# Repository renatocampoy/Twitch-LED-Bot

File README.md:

## Twitch LED Bot - ESP8266

Criado por Eng. Renato Campoy.

Este projeto permite que você controle um strip de LED NeoPixel via comandos no chat da Twitch, utilizando a placa ESP8266. O código é escrito em C++ e utiliza a biblioteca WiFiManager para gerenciar a conexão Wi-Fi e a biblioteca Adafruit NeoPixel para controlar o strip de LED.

## Token da Twitch

Para usar este código, você precisará de um token de OAuth da Twitch. Aqui estão as etapas para obtê-lo:

1.  Acesse [https://twitchapps.com/tmi/](https://twitchapps.com/tmi/)
2.  Clique em 'Connect' e autorize o acesso ao seu canal.
3.  Copie o token gerado. Este é o seu token OAuth, que permite que o bot envie mensagens ao seu canal.

Tenha em mente que este token é equivalente à senha da sua conta da Twitch. Não compartilhe com ninguém.

### Dependências

Você precisará das seguintes bibliotecas para usar este projeto:

-   ESP8266WiFi
-   DNSServer
-   ESP8266WebServer
-   WiFiManager
-   EEPROM
-   Adafruit_NeoPixel

Estas bibliotecas podem ser instaladas através do Gerenciador de Bibliotecas do Arduino.

## Instalação

1.  Clone este repositório.
2.  Abra o arquivo `.ino` no Arduino IDE.
3.  Carregue o código para o ESP8266.

## Configuração

1.  Ao ligar o ESP, uma rede wifi com o nome LEDBOT_AP aparecerá, conecte-se a ela.
2.  Ao conectar, aparecerá uma pagina onde você deve clicar em "Configure WIFI"
3.  Clique na sua REDE, entre com a senha.
4. Em "Nick" é o seu usuário da Twitch tudo em minúsculo 
5. Em Token você vai colocar o token gerado no tópico "Token da Twitch"

## Uso

Uma vez que o código esteja funcionando, você poderá enviar comandos para o chat da Twitch para controlar a iluminação do strip de LED. Aqui estão alguns exemplos de comandos que você pode usar:

-   `!led vermelho`: muda a cor do LED para vermelho.
-   `!led #ff00ff`: muda a cor do LED para o valor hexadecimal fornecido (neste caso, magenta).
-   `!led cores`: lista todas as cores disponíveis.

Além disso, o bot responde a comandos enviados via interface serial para reiniciar o ESP ou redefinir as configurações de WiFi ou Twitch. (vide código)

## Contribuição

Este é um projeto open-source. Se tiver alguma sugestão ou melhoria, por favor, faça um fork do repositório e envie uma pull request.

## Problemas Conhecidos

Atualmente, o bot não responde a erros do servidor da Twitch. Se você experimentar algum problema, tente reiniciar o ESP.

## Licença

Este projeto está licenciado sob a Licença GPLv3 - veja o arquivo [LICENSE](https://www.gnu.org/licenses/gpl-3.0.pt-br.html) para mais detalhes.

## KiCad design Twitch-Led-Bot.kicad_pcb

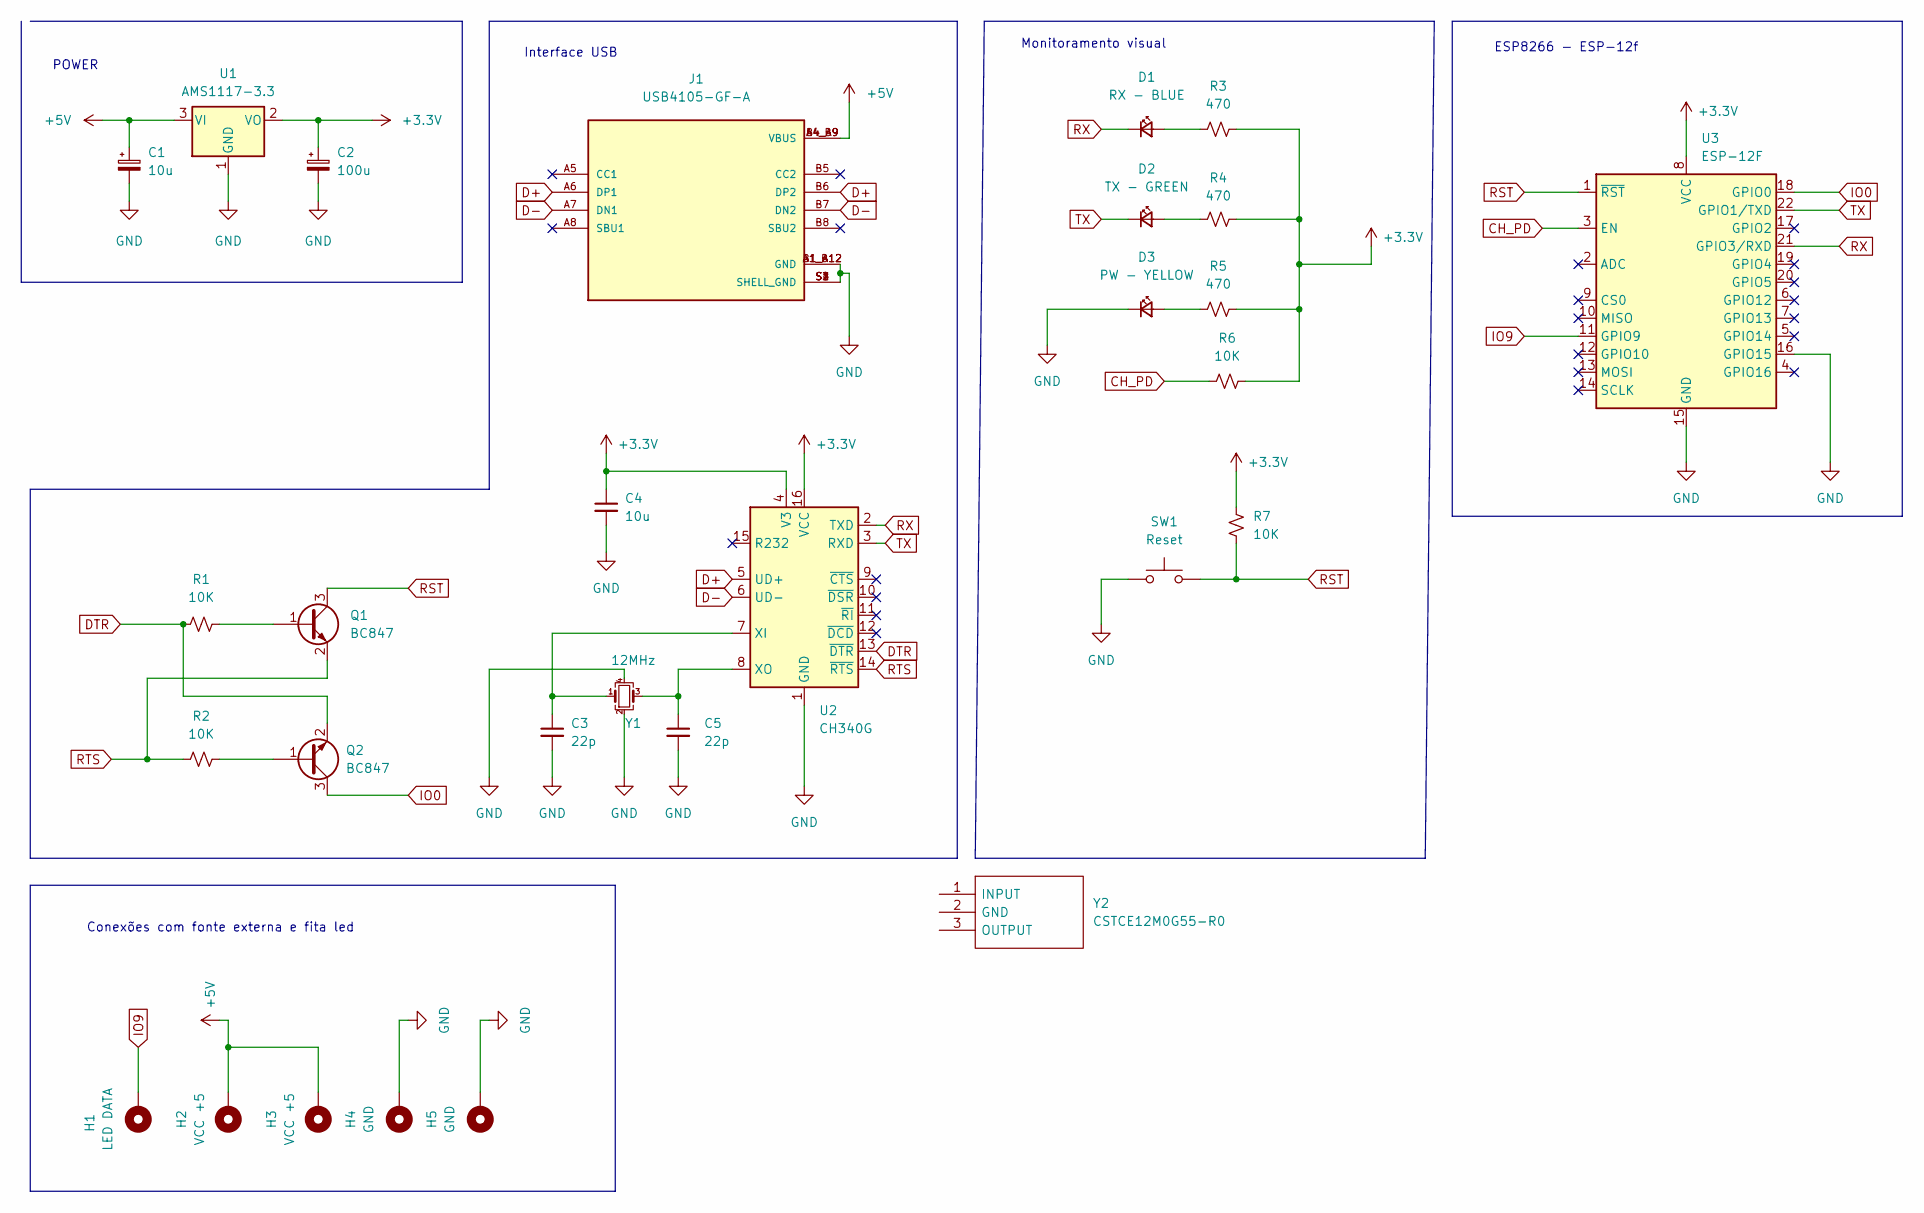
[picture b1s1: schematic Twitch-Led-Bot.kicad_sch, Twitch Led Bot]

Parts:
C1, C4: 10u; C_0805_2012Metric
C2: 100u; C_0805_2012Metric
C3, C5: 22p; C_0805_2012Metric
D1: RX - BLUE; LED_0805_2012Metric
D2: TX - GREEN; LED_0805_2012Metric
D3: PW - YELLOW; LED_0805_2012Metric
H1: LED DATA; MountingHole_2.1mm
H2, H3: VCC +5; MountingHole_2.1mm
H4, H5: GND; MountingHole_2.1mm
J1: USB4105-GF-A; GCT_USB4105-GF-A; PARTREV A3
Q1, Q2: BC847; SOT-23
R1, R2, R6, R7: 10K; R_0805_2012Metric
R3, R4, R5: 470; R_0805_2012Metric
SW1: Reset; SW_Push_SPST_NO_Alps_SKRK
U1: AMS1117-3.3; SOT-223-3_TabPin2
U2: CH340G; SOIC-16_3.9x9.9mm_P1.27mm
U3: ESP-12F; ESP-12E
Y1: 12MHz; Crystal_SMD_2520-4Pin_2.5x2.0mm
Y2: CSTCE12M0G55-R0; CSTCE12M0G55R0; Manufacturer_Part_Number CSTCE12M0G55-R0; Mouser Part Number 81-CSTCE12M0G55-R0

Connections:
+3V3: C2.1, C4.1, R3.2, R4.2, R5.2, R6.2, R7.2, U1.2 (VO), U2.4 (V3), U2.16 (VCC), U3.8 (VCC)
+5V: C1.1, H2.1, H3.1, J1.A4_B9 (VBUS), J1.B4_A9 (VBUS), U1.3 (VI)
CH_PD: R6.1, U3.3 (EN)
D+: J1.A6 (DP1), J1.B6 (DP2), U2.5 (UD+)
D-: J1.A7 (DN1), J1.B7 (DN2), U2.6 (UD-)
DTR: Q2.2 (E), R1.1, U2.13 (~DTR)
GND: C1.2, C2.2, C3.2, C4.2, C5.2, D3.1 (K), H4.1, H5.1, J1.A1_B12 (GND), J1.B1_A12 (GND), J1.S1 (SHELL_GND), J1.S2 (SHELL_GND), J1.S3 (SHELL_GND), J1.S4 (SHELL_GND), SW1.1, U1.1 (GND), U2.1 (GND), U3.15 (GND), U3.16 (GPIO15), Y1.2, Y1.4
IO0: Q2.3 (C), U3.18 (GPIO0)
IO9: H1.1, U3.11 (GPIO9)
unnamed: C3.1, U2.7 (XI), Y1.1
unnamed: C5.1, U2.8 (XO), Y1.3
unnamed: D1.2 (A), R3.1
unnamed: D2.2 (A), R4.1
unnamed: D3.2 (A), R5.1
unnamed: Q1.1 (B), R1.2
unnamed: Q2.1 (B), R2.2
RST: Q1.3 (C), R7.1, SW1.2, U3.1 (~RST)
RTS: Q1.2 (E), R2.1, U2.14 (~RTS)
RX: D1.1 (K), U2.2 (TXD), U3.21 (GPIO3/RXD)
TX: D2.1 (K), U2.3 (RXD), U3.22 (GPIO1/TXD)

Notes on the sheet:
Conexões com fonte externa e fita led
ESP8266 - ESP-12f
Interface USB
POWER
Monitoramento visual

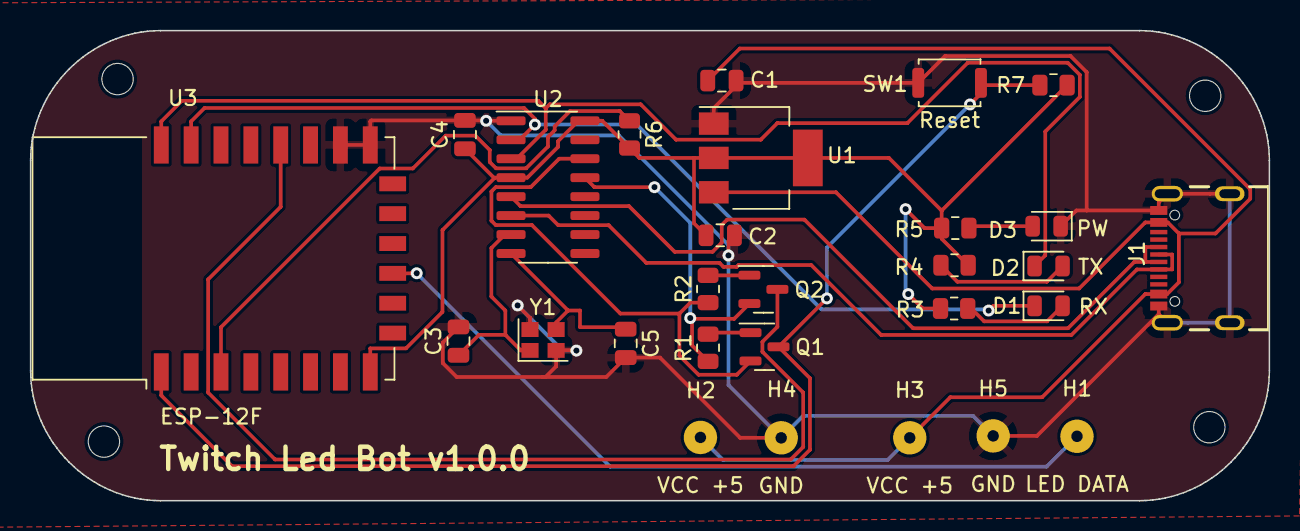
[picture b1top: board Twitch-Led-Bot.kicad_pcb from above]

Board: 2 copper layers, 83.0 x 31.5 mm, 28 parts (0 on the bottom side), 20 nets.

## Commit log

2023-06-29 Bug correction v.1.0.1
    Correction in the wiring diagram with the microcontroller connecting GP015 to GND
2023-06-30 Bug correction v.1.0.2
    RX LED has problems on the trail in the schematic

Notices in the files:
Twitch-Led-Bot.kicad_pcb:
License: GPLv3
